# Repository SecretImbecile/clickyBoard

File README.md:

# clickyBoard
A Raspberry Pi add-on board that adds a simple switch and LED circuit for GPIO programming, using mechanical keyboard switches

Read the [documentation file](Documentation/clickyBoard.pdf).

## Keyboard.pretty

Kicad files uses [Keyboard.pretty](https://github.com/stormbard/Keyboard.pretty), the KiCad Module Repository for keyboard PCB creation.

## FAQ

### What does clickyBoard add to my Pi?

clickyBoard adds a simple circuit to your Raspberry Pi for GPIO programming, featuring four input switches, as well as LED backlighting which can be controlled with a single output.

The board uses Cherry MX compatible switches, which are popular keyboard switches, that are widely and cheaply available along with compatible keycaps.

### Has the design been tested?

clickyBoard version 1.0 was manufactured and tested, and the discovered errors were rectified in board version 1.1. This latest version has not been manufactured as of yet, so please perform your own checks before sending the design off to be manufactured.

### Is this a HAT?

Not quite. The Raspberry Pi HAT [specification](https://github.com/raspberrypi/hats) requires a HAT to have an ID EEPROM. To keep this add-on board simple to assemble, this has been ommited. The clickyboard does adhere to the HAT mechanical specifications.

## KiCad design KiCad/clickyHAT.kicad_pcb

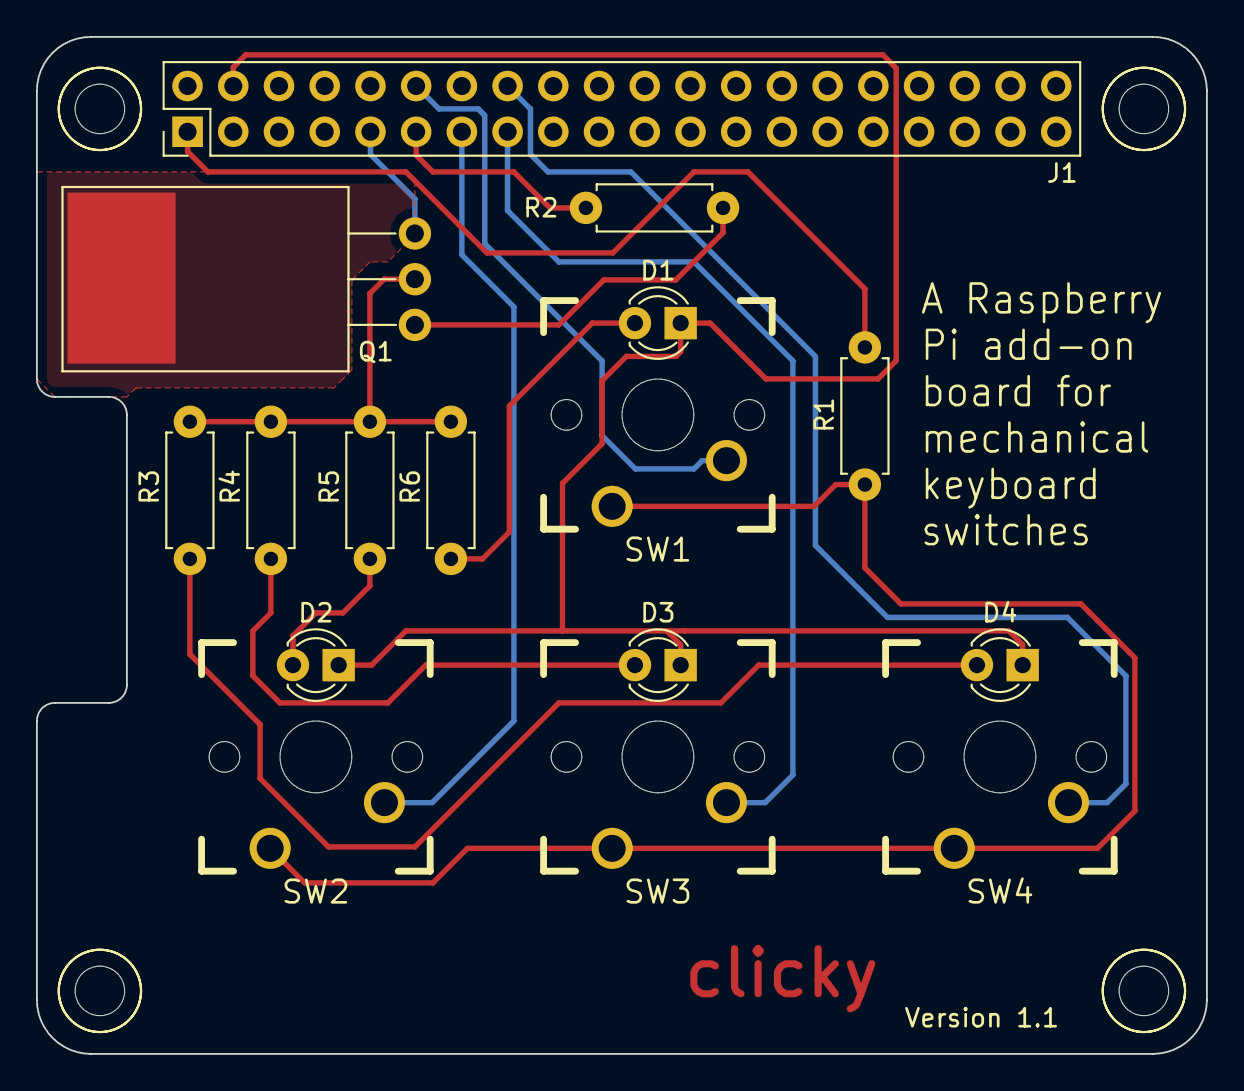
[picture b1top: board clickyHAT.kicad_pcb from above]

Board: 2 copper layers, 65.0 x 56.5 mm, 24 parts (0 on the bottom side), 15 nets.

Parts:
D1, D2, D3, D4: LED; LED_D3.0mm
J1: Raspberry_Pi_2_3; Pin_Header_Straight_2x20_Pitch2.54mm
MNT1, MNT2, MNT3, MNT4: 1pin
MNTB1, MNTB2, MNTB3, MNTB4: 1pin
Q1: BS170; TO-220_Horizontal
R1, R2: 1K; R_Axial_DIN0207_L6.3mm_D2.5mm_P7.62mm_Horizontal
R3, R4, R5, R6: 150; R_Axial_DIN0207_L6.3mm_D2.5mm_P7.62mm_Horizontal
SW1, SW2, SW3, SW4: SW_Push; CHERRY_PCB_100H

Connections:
unnamed: D1.1, R6.1
unnamed: D1.2, D2.2, D3.2, D4.2, J1.4
unnamed: D2.1, R5.1
unnamed: D3.1, R4.1
unnamed: D4.1, R3.1
unnamed: J1.1, R1.1
unnamed: J1.9, Q1.3
unnamed: J1.11, R2.1
unnamed: J1.12, SW1.2
unnamed: J1.13, SW2.2
unnamed: J1.15, SW3.2
unnamed: J1.16, SW4.2
unnamed: Q1.2, Q1.4, R3.2, R4.2, R5.2, R6.2
unnamed: Q1.1, R2.2
unnamed: R1.2, SW1.1, SW2.1, SW3.1, SW4.1

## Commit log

2017-07-20 removed board logo until license is decided
2017-07-20 Started Documentation
2017-07-21 Completed Documentation
2017-07-21 added license
    renamed documentation
2017-07-21 added documentation link in README.md
2017-07-22 Updated board design
    removed copper fill, updated gerbers are included
2017-07-22 updated render
2017-07-22 updated board text
2017-07-22 added kicad module link to README.md
2017-07-22 Updated PCB layout in documentation
    removed copper fill
2017-07-22 Clarified design rules
2017-07-24 Updated board error information
2017-08-05 Revision 1.1
2017-08-05 Documentation updated
2017-08-07 Rotated switches
    crazy routing

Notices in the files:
KiCad/clickyHAT.kicad_pcb:
CC BY-SA 4.0
